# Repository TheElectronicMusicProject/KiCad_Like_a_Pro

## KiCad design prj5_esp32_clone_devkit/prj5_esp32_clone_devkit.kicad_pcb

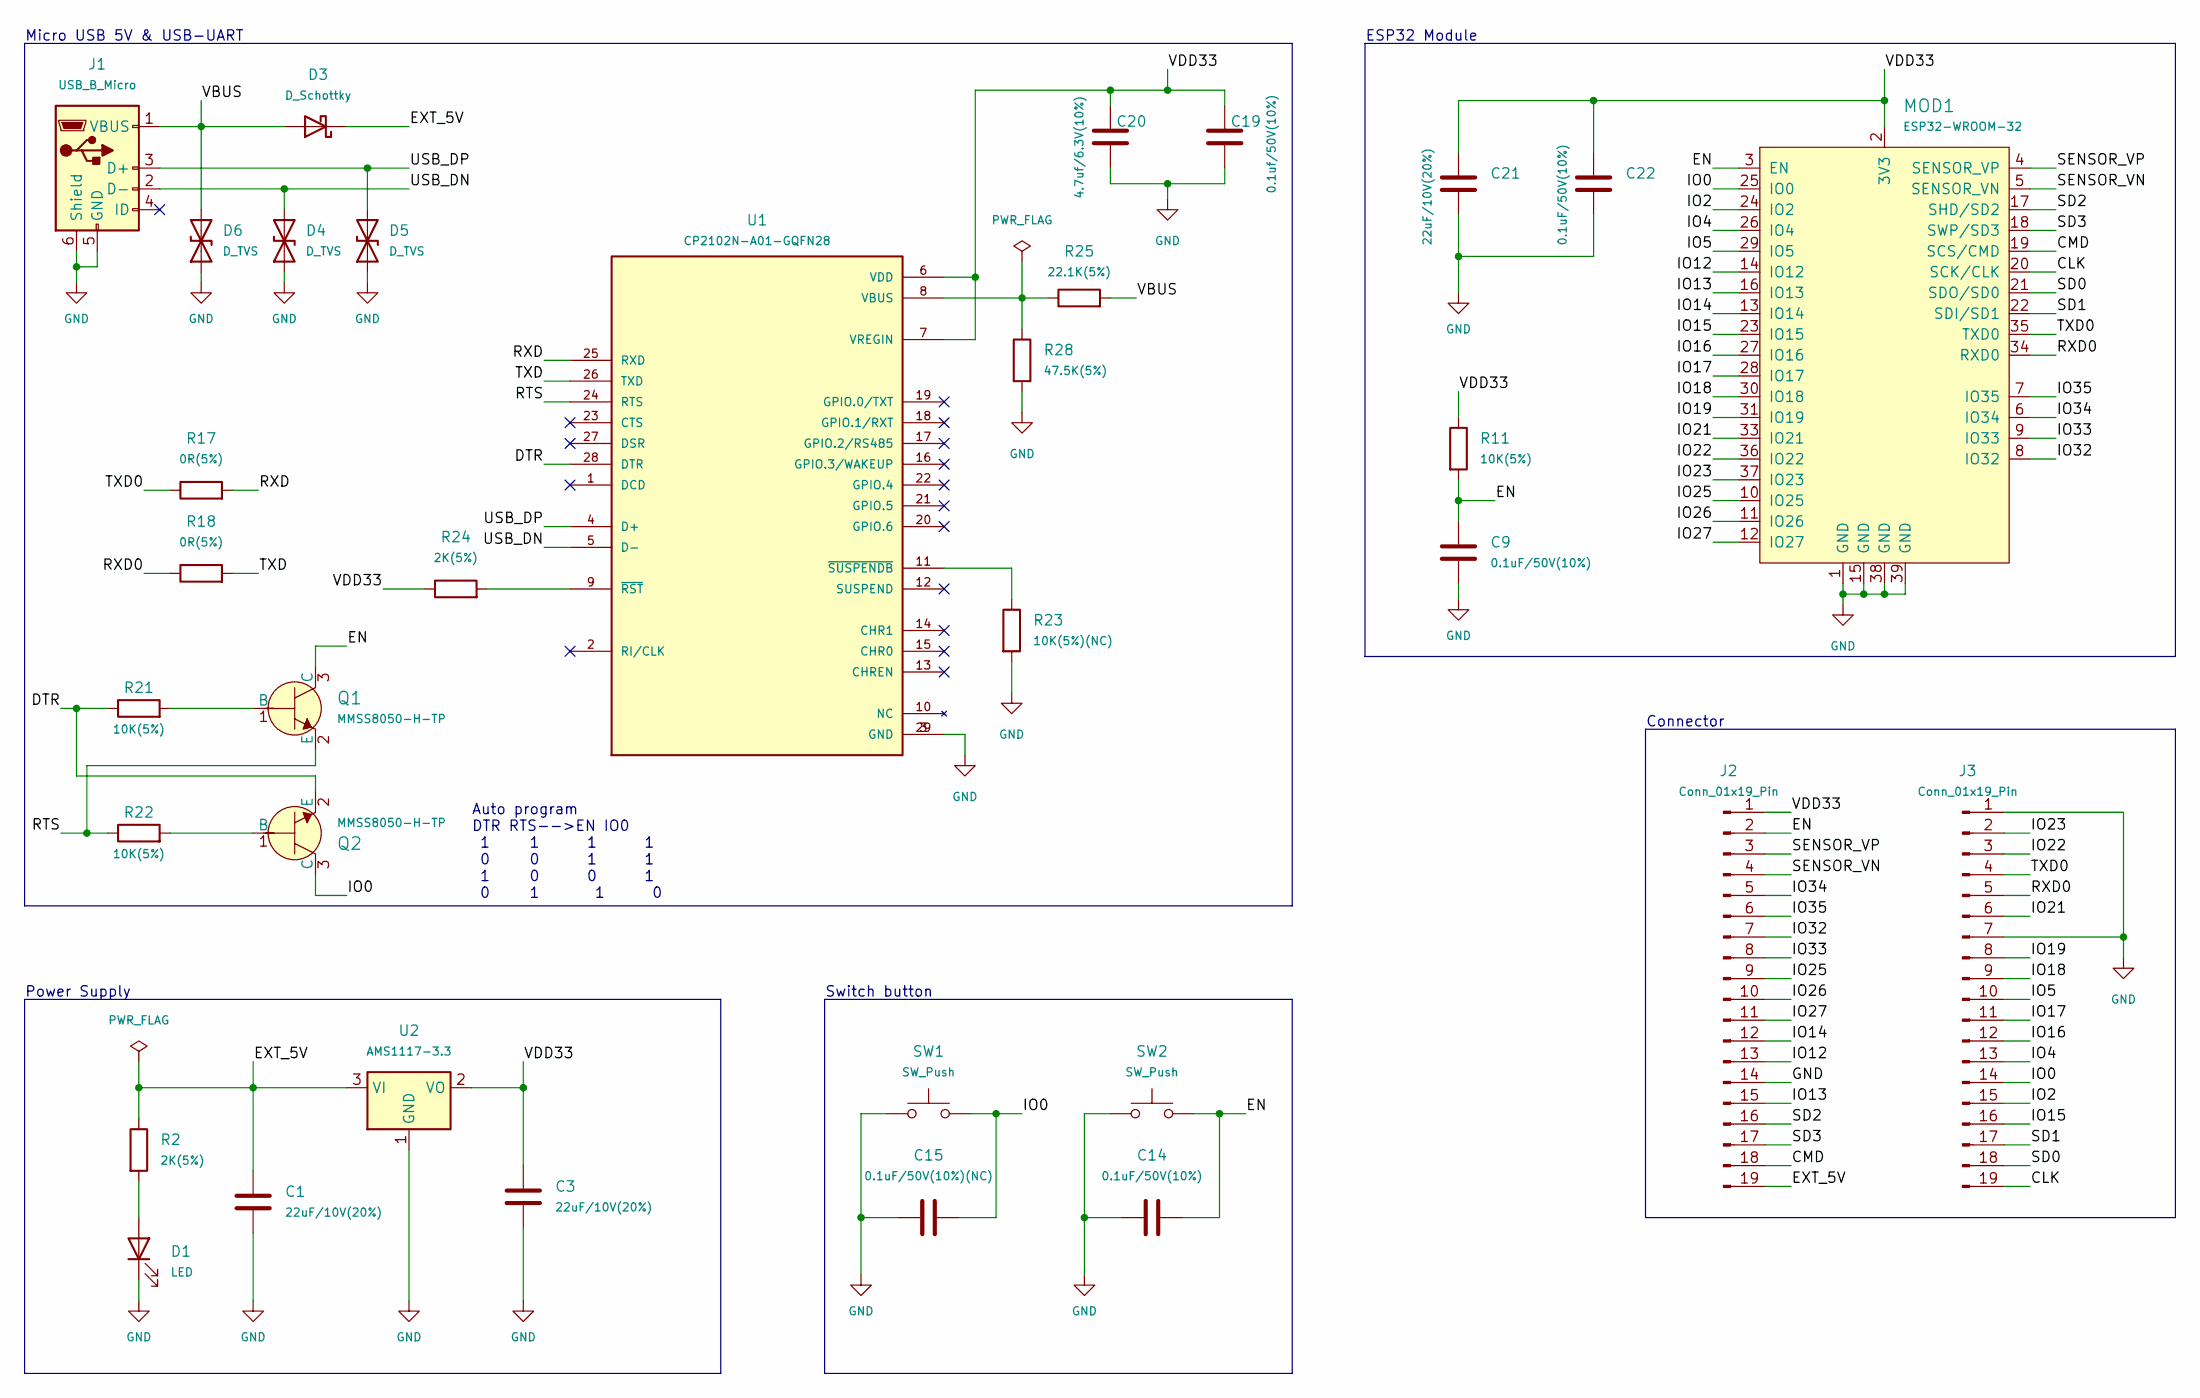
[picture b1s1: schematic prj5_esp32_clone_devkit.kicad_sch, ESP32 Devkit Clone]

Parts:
C1, C3, C21: 22uF/10V(20%); C_0603_1608Metric
C9, C14, C22: 0.1uF/50V(10%); C_0402_1005Metric
C15: 0.1uF/50V(10%)(NC); C_0402_1005Metric
C19: 0.1uf/50V(10%); C_0402_1005Metric
C20: 4.7uf/6.3V(10%); C_0402_1005Metric
D1: LED; LED_0603_1608Metric
D3: D_Schottky; D_SOD-323
D4, D5, D6: D_TVS; D_SOD-523
J1: USB_B_Micro; USB_Micro-AB_Molex_47590-0001
J2, J3: Conn_01x19_Pin; PinHeader_1x19_P2.54mm_Vertical
MOD1: ESP32-WROOM-32; ESP32-WROOM-32D; MPN ESP32-WROOM-32; Digi-Key_PN 1904-1010-1-ND
Q1, Q2: MMSS8050-H-TP; SOT-23-3; MPN MMSS8050-H-TP; Digi-Key_PN MMSS8050-H-TPMSCT-ND
R2, R24: 2K(5%); R_01005_0402Metric
R11, R21, R22: 10K(5%); R_01005_0402Metric
R17, R18: 0R(5%); R_01005_0402Metric
R23: 10K(5%)(NC); R_01005_0402Metric
R25: 22.1K(5%); R_01005_0402Metric
R28: 47.5K(5%); R_01005_0402Metric
SW1, SW2: SW_Push; SW_SPST_B3S-1000
U1: CP2102N-A01-GQFN28; TQFN-28-1EP_5x5mm_P0.5mm_EP2.7x2.7mm; PARTREV 1.0
U2: AMS1117-3.3; SOT-223-3_TabPin2

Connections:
/CLK: J3.19, MOD1.20 (SCK/CLK)
/CMD: J2.18, MOD1.19 (SCS/CMD)
/DTR: Q2.2 (E), R21.1, U1.28 (DTR)
/EN: C9.1, C14.2, J2.2, MOD1.3 (EN), Q1.3 (C), R11.2, SW2.2
/EXT_5V: C1.1, D3.1 (K), J2.19, R2.1, U2.3 (VI)
/IO0: C15.2, J3.14, MOD1.25 (IO0), Q2.3 (C), SW1.2
/IO2: J3.15, MOD1.24 (IO2)
/IO4: J3.13, MOD1.26 (IO4)
/IO5: J3.10, MOD1.29 (IO5)
/IO12: J2.13, MOD1.14 (IO12)
/IO13: J2.15, MOD1.16 (IO13)
/IO14: J2.12, MOD1.13 (IO14)
/IO15: J3.16, MOD1.23 (IO15)
/IO16: J3.12, MOD1.27 (IO16)
/IO17: J3.11, MOD1.28 (IO17)
/IO18: J3.9, MOD1.30 (IO18)
/IO19: J3.8, MOD1.31 (IO19)
/IO21: J3.6, MOD1.33 (IO21)
/IO22: J3.3, MOD1.36 (IO22)
/IO23: J3.2, MOD1.37 (IO23)
/IO25: J2.9, MOD1.10 (IO25)
/IO26: J2.10, MOD1.11 (IO26)
/IO27: J2.11, MOD1.12 (IO27)
/IO32: J2.7, MOD1.8 (IO32)
/IO33: J2.8, MOD1.9 (IO33)
/IO34: J2.5, MOD1.6 (IO34)
/IO35: J2.6, MOD1.7 (IO35)
/RTS: Q1.2 (E), R22.1, U1.24 (RTS)
/RXD: R17.2, U1.25 (RXD)
/RXD0: J3.5, MOD1.34 (RXD0), R18.1
/SD0: J3.18, MOD1.21 (SDO/SD0)
/SD1: J3.17, MOD1.22 (SDI/SD1)
/SD2: J2.16, MOD1.17 (SHD/SD2)
/SD3: J2.17, MOD1.18 (SWP/SD3)
/SENSOR_VN: J2.4, MOD1.5 (SENSOR_VN)
/SENSOR_VP: J2.3, MOD1.4 (SENSOR_VP)
/TXD: R18.2, U1.26 (TXD)
/TXD0: J3.4, MOD1.35 (TXD0), R17.1
/USB_DN: D4.2 (A2), J1.2 (D-), U1.5 (D-)
/USB_DP: D5.2 (A2), J1.3 (D+), U1.4 (D+)
/VBUS: D3.2 (A), D6.2 (A2), J1.1 (VBUS), R25.2
/VDD33: C3.1, C19.1, C20.1, C21.1, C22.1, J2.1, MOD1.2 (3V3), R11.1, R24.1, U1.6 (VDD), U1.7 (VREGIN), U2.2 (VO)
GND: C1.2, C3.2, C9.2, C14.1, C15.1, C19.2, C20.2, C21.2, C22.2, D1.1 (K), D4.1 (A1), D5.1 (A1), D6.1 (A1), J1.5 (GND), J1.6 (Shield), J2.14, J3.1, J3.7, MOD1.1 (GND), MOD1.15 (GND), MOD1.38 (GND), MOD1.39 (GND), R23.2, R28.2, SW1.1, SW2.1, U1.3 (GND), U1.29 (GND), U2.1 (GND)
unnamed: D1.2 (A), R2.2
unnamed: Q1.1 (B), R21.2
unnamed: Q2.1 (B), R22.2
unnamed: R25.1, R28.1, U1.8 (VBUS)
unnamed: R24.2, U1.9 (~RST)
unnamed: R23.1, U1.11 (~SUSPENDB)

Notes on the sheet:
Switch button
Micro USB 5V & USB-UART
Power Supply
Auto program DTR RTS-->EN IO0 1 1 1 1 0 0 1 1 1 0 0 1 0 1 1 0
Connector
ESP32 Module

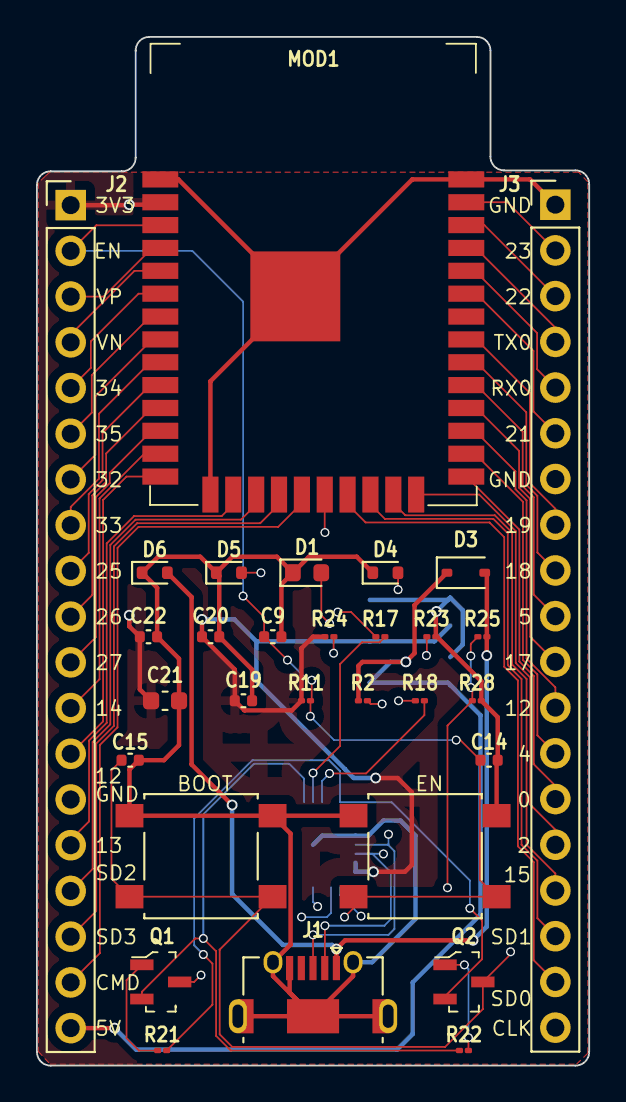
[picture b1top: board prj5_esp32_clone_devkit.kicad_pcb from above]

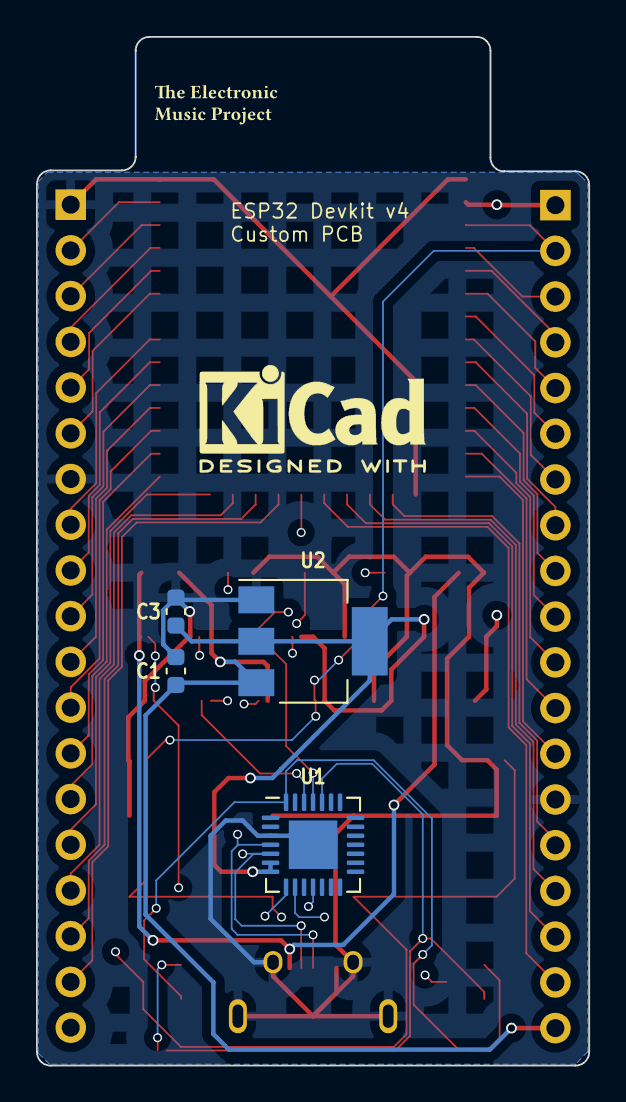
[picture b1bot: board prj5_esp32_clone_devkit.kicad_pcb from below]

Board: 4 copper layers, 30.7 x 57.2 mm, 36 parts (6 on the bottom side), 49 nets.

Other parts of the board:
G1: LOGO; The_Electronic_Music_Project_silk_logo
REF1: KiCad-Logo2_5mm_SilkScreen

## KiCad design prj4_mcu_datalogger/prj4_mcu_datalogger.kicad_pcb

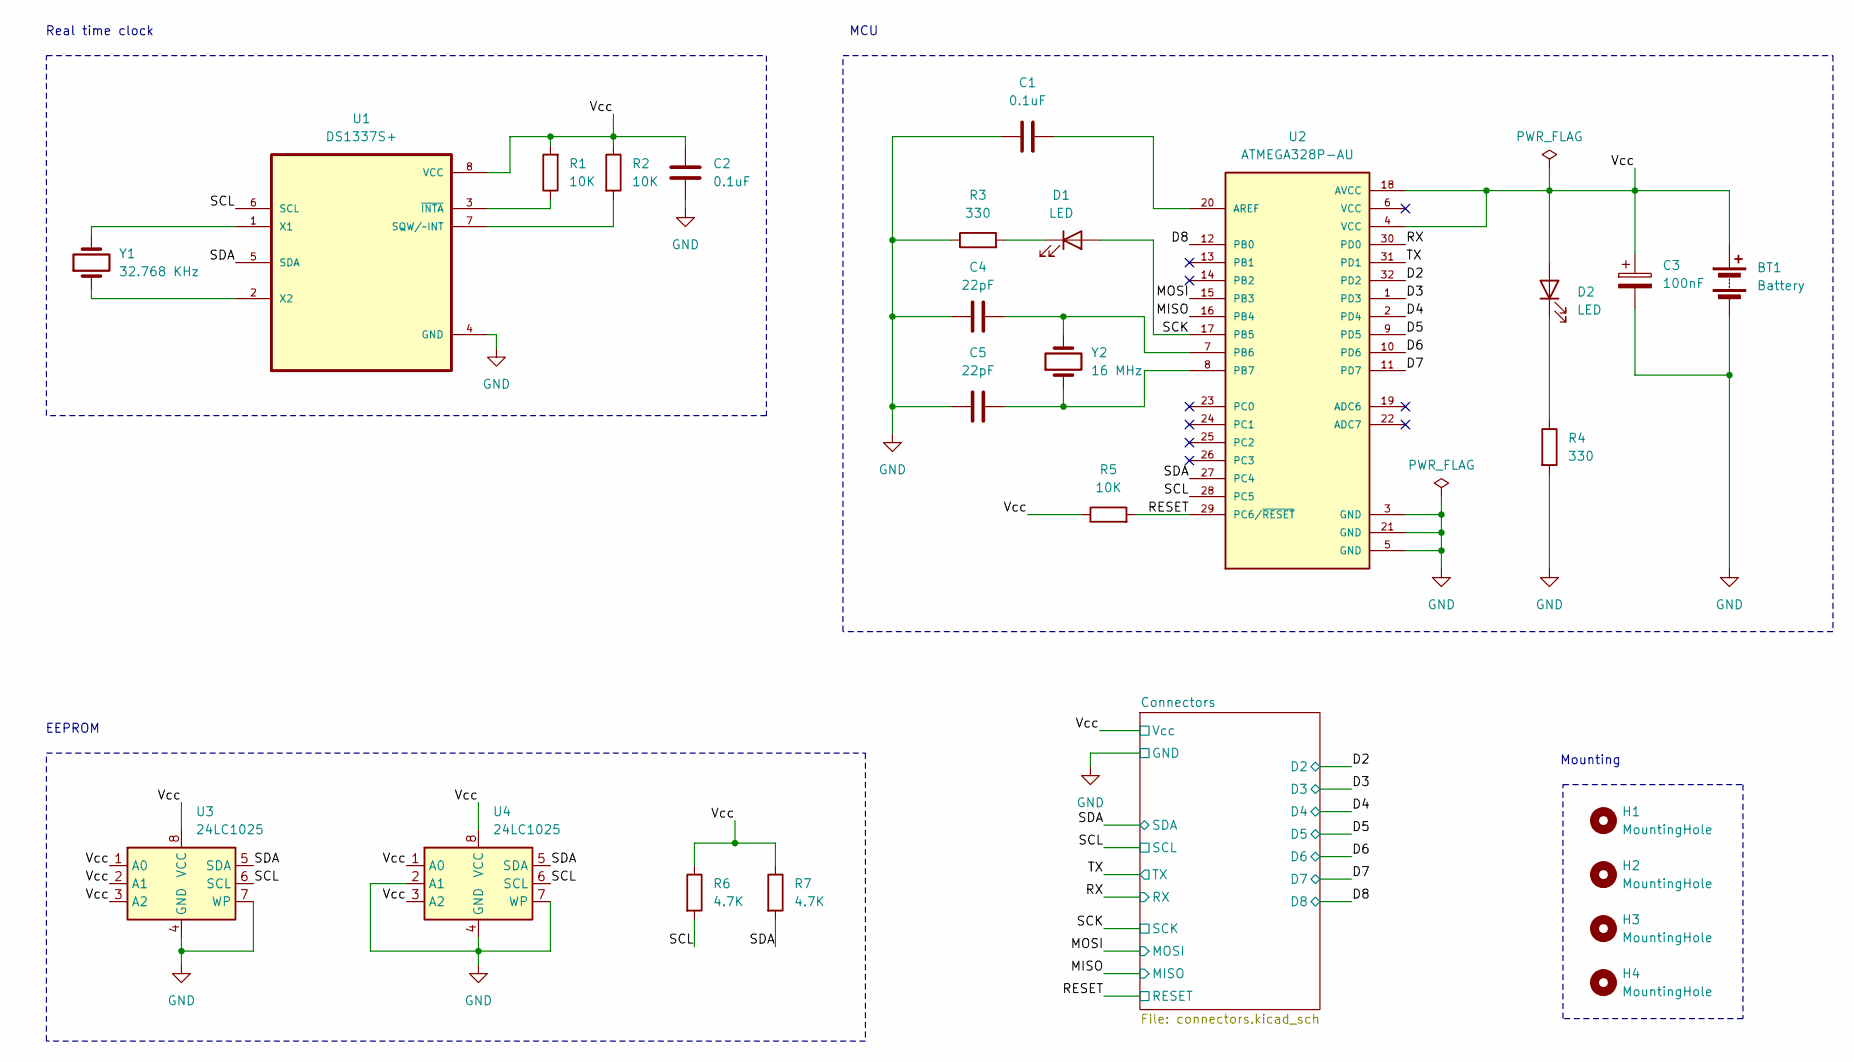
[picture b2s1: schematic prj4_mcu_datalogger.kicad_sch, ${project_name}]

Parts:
BT1: Battery; PinHeader_1x02_P2.54mm_Vertical
C1, C2: 0.1uF; C_0805_2012Metric
C3: 100nF; C_0805_2012Metric
C4, C5: 22pF; C_0805_2012Metric
D1, D2: LED; LED_0805_2012Metric
H1, H2, H3, H4: MountingHole; MountingHole_2.1mm
R1, R2, R5: 10K; R_0805_2012Metric
R3, R4: 330; R_0805_2012Metric
R6, R7: 4.7K; R_0805_2012Metric
U1: DS1337S+; SOIC127P600X175-8N
U2: ATMEGA328P-AU; QFP80P900X900X120-32N
U3, U4: 24LC1025; SOIC-8_5.23x5.23mm_P1.27mm
Y1: 32.768 KHz; Crystal_SMD_5032-2Pin_5.0x3.2mm_HandSoldering
Y2: 16 MHz; Crystal_SMD_5032-2Pin_5.0x3.2mm_HandSoldering

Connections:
/D2: U2.32 (PD2); also elsewhere on the board
/D3: U2.1 (PD3); also elsewhere on the board
/D4: U2.2 (PD4); also elsewhere on the board
/D5: U2.9 (PD5); also elsewhere on the board
/D6: U2.10 (PD6); also elsewhere on the board
/D7: U2.11 (PD7); also elsewhere on the board
/D8: U2.12 (PB0); also elsewhere on the board
/MISO: U2.16 (PB4); also elsewhere on the board
/MOSI: U2.15 (PB3); also elsewhere on the board
/RESET: R5.2, U2.29 (PC6/~RESET); also elsewhere on the board
/RX: U2.30 (PD0); also elsewhere on the board
/SCK: D1.2 (A), U2.17 (PB5); also elsewhere on the board
/SCL: R6.2, U1.6 (SCL), U2.28 (PC5), U3.6 (SCL), U4.6 (SCL); also elsewhere on the board
/SDA: R7.2, U1.5 (SDA), U2.27 (PC4), U3.5 (SDA), U4.5 (SDA); also elsewhere on the board
/TX: U2.31 (PD1); also elsewhere on the board
/Vcc: BT1.1 (+), C2.1, C3.1, D2.2 (A), R1.2, R2.1, R5.1, R6.1, R7.1, U1.8 (VCC), U2.4 (VCC), U2.18 (AVCC), U3.1 (A0), U3.2 (A1), U3.3 (A2), U3.8 (VCC), U4.1 (A0), U4.3 (A2), U4.8 (VCC); also elsewhere on the board
GND: BT1.2 (-), C1.1, C2.2, C3.2, C4.1, C5.1, R3.1, R4.2, U1.4 (GND), U2.3 (GND), U2.5 (GND), U2.21 (GND), U3.4 (GND), U3.7 (WP), U4.2 (A1), U4.4 (GND), U4.7 (WP); also elsewhere on the board
unnamed: D1.1 (K), R3.2
unnamed: D2.1 (K), R4.1
unnamed: R2.2, U1.7 (SQW/~INT)
unnamed: U1.1 (X1), Y1.2
unnamed: U1.2 (X2), Y1.1
unnamed: R1.1, U1.3 (~INTA)
unnamed: C1.2, U2.20 (AREF)
unnamed: C4.2, U2.7 (PB6), Y2.2
unnamed: C5.2, U2.8 (PB7), Y2.1

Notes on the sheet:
MCU
Mounting
Real time clock
EEPROM

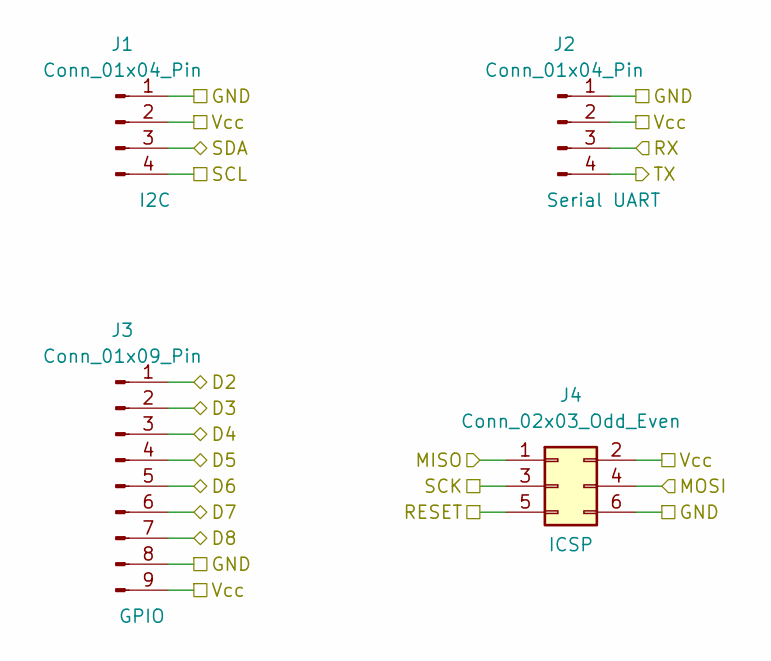
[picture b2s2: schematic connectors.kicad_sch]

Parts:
J1, J2: Conn_01x04_Pin; PinHeader_1x04_P2.54mm_Vertical
J3: Conn_01x09_Pin; PinHeader_1x09_P2.54mm_Vertical
J4: Conn_02x03_Odd_Even; PinHeader_2x03_P2.54mm_Vertical

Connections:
/D2: J3.1; also elsewhere on the board
/D3: J3.2; also elsewhere on the board
/D4: J3.3; also elsewhere on the board
/D5: J3.4; also elsewhere on the board
/D6: J3.5; also elsewhere on the board
/D7: J3.6; also elsewhere on the board
/D8: J3.7; also elsewhere on the board
/MISO: J4.1; also elsewhere on the board
/MOSI: J4.4; also elsewhere on the board
/RESET: J4.5; also elsewhere on the board
/RX: J2.3; also elsewhere on the board
/SCK: J4.3; also elsewhere on the board
/SCL: J1.4; also elsewhere on the board
/SDA: J1.3; also elsewhere on the board
/TX: J2.4; also elsewhere on the board
/Vcc: J1.2, J2.2, J3.9, J4.2; also elsewhere on the board
GND: J1.1, J2.1, J3.8, J4.6; also elsewhere on the board

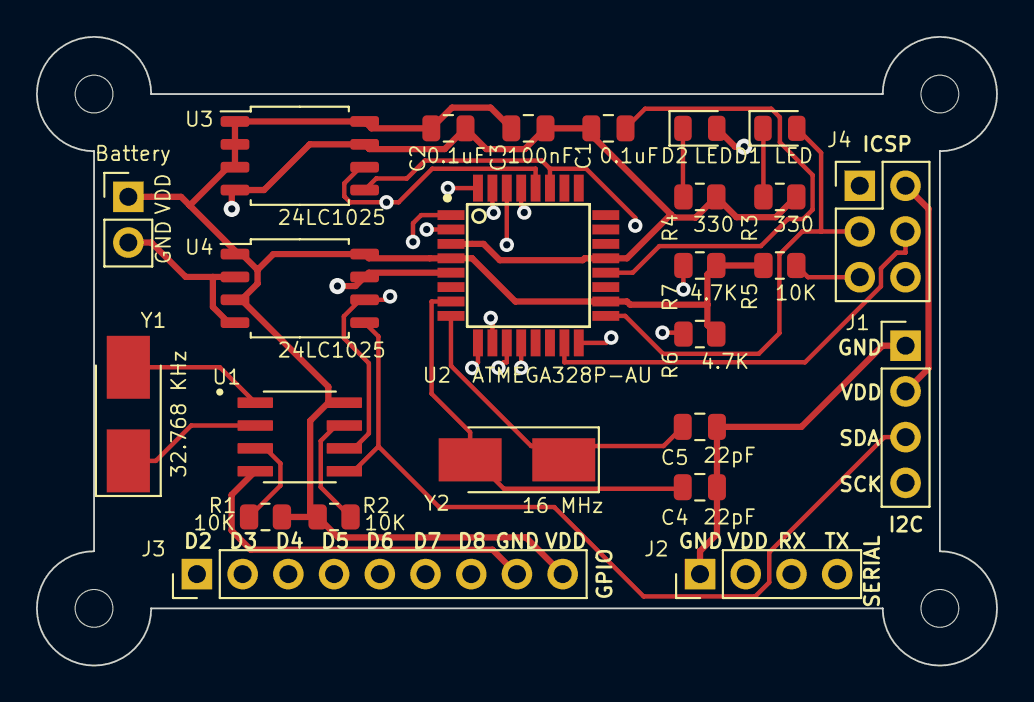
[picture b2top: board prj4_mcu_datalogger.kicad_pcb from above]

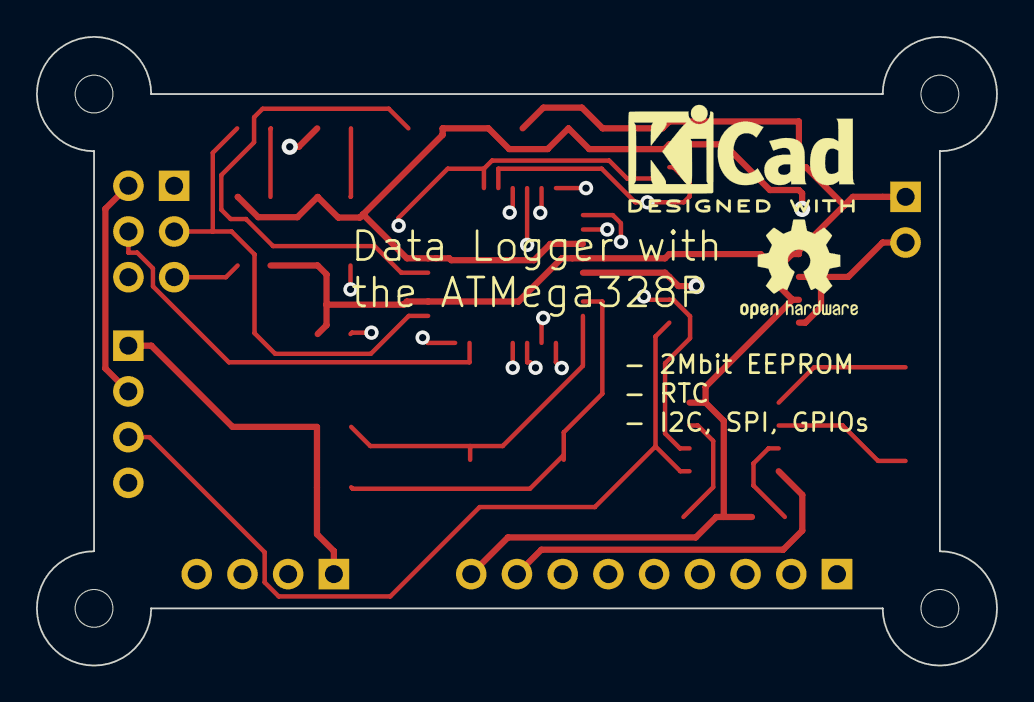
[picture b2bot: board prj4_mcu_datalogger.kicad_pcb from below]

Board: 4 copper layers, 53.3 x 34.9 mm, 31 parts (2 on the bottom side), 26 nets.

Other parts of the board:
REF1: KiCad-Logo2_5mm_SilkScreen
REF2: OSHW-Logo2_7.3x6mm_SilkScreen

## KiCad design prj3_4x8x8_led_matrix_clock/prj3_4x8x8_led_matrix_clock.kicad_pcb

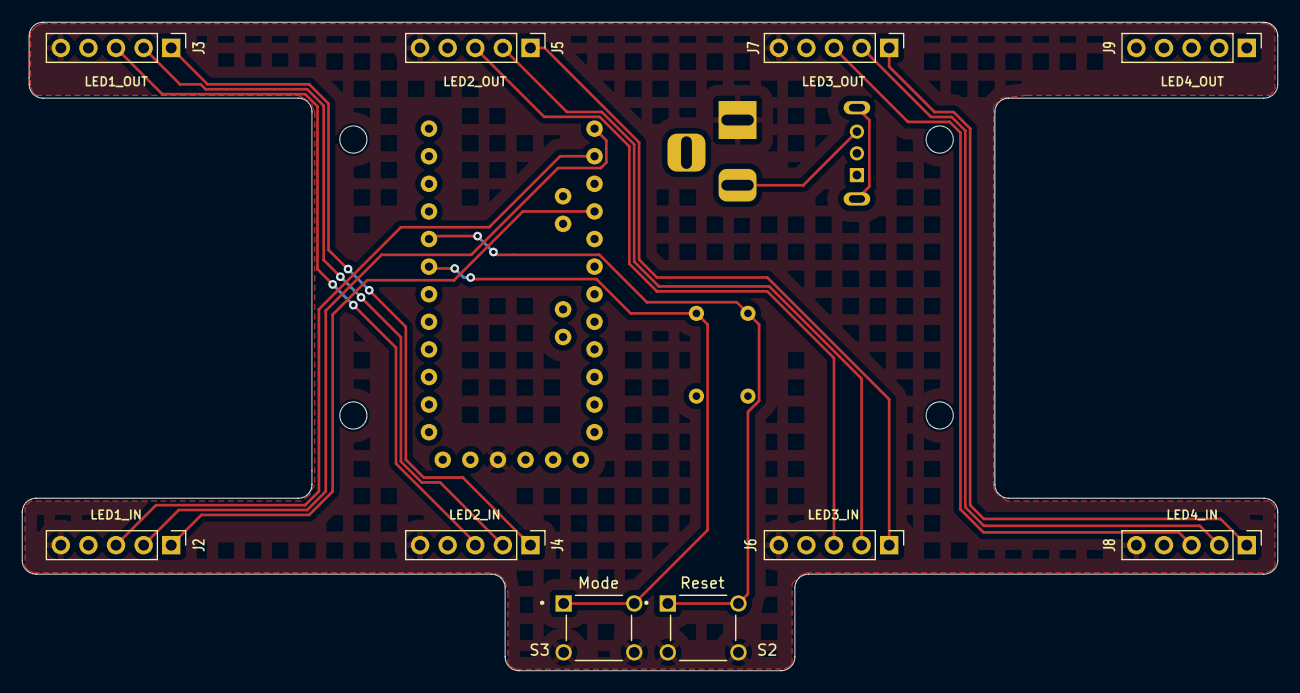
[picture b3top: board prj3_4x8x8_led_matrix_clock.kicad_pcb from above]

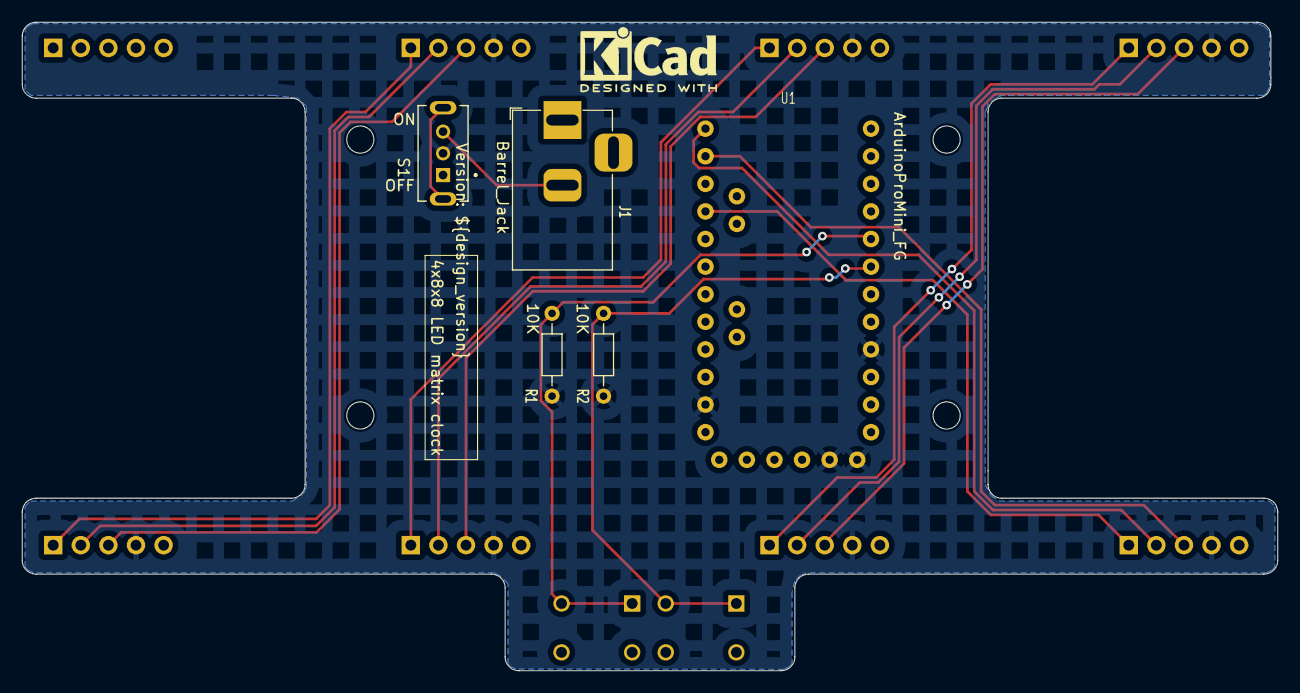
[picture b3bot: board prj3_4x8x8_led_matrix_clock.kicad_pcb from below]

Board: 2 copper layers, 115.6 x 59.7 mm, 19 parts (5 on the bottom side), 17 nets.

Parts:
H1, H2, H3, H4: MountingHole; MountingHole_2.5mm
J1: Barrel_Jack; BarrelJack_Horizontal
J2: LED1_IN; PinHeader_1x05_P2.54mm_Vertical
J3: LED1_OUT; PinHeader_1x05_P2.54mm_Vertical
J4: LED2_IN; PinHeader_1x05_P2.54mm_Vertical
J5: LED2_OUT; PinHeader_1x05_P2.54mm_Vertical
J6: LED3_IN; PinHeader_1x05_P2.54mm_Vertical
J7: LED3_OUT; PinHeader_1x05_P2.54mm_Vertical
J8: LED4_IN; PinHeader_1x05_P2.54mm_Vertical
J9: LED4_OUT; PinHeader_1x05_P2.54mm_Vertical
R1, R2: 10K; R_Axial_DIN0204_L3.6mm_D1.6mm_P7.62mm_Horizontal
S1: SS12D07VG4; SW_SS12D07VG4
S2, S3: 1825967-1; SW_1825967-1
U1: ArduinoProMini_FG

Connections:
/CLK0: J2.1, U1.6 (SCK)
/CLK1: J3.1, J4.1
/CLK2: J5.1, J6.1
/CLK3: J7.1, J8.1
/CS0: J2.2, U1.17 (D10)
/CS1: J3.2, J4.2
/CS2: J5.2, J6.2
/CS3: J7.2, J8.2
/DIN0: J2.3, U1.8 (MOSI)
/DIN1: J3.3, J4.3
/DIN2: J5.3, J6.3
/DIN3: J7.3, J8.3
/MODE_SELECT: R2.2, S3.1, S3.2, U1.11 (D4)
/TIMER_RESET: R1.2, S2.1, S2.2, U1.12 (D5)
/Vcc: J1.1, J2.5, J3.5, J4.5, J5.5, J6.5, J7.5, J8.5, S2.3, S2.4, S3.3, S3.4, U1.1 (Vcc)
GND: J2.4, J3.4, J4.4, J5.4, J6.4, J7.4, J8.4, R1.1, R2.1, S1.2, U1.18 (GND_2), U1.19 (GND_1), U1.20 (GND), U1.21 (GND)
unnamed: J1.2, S1.3

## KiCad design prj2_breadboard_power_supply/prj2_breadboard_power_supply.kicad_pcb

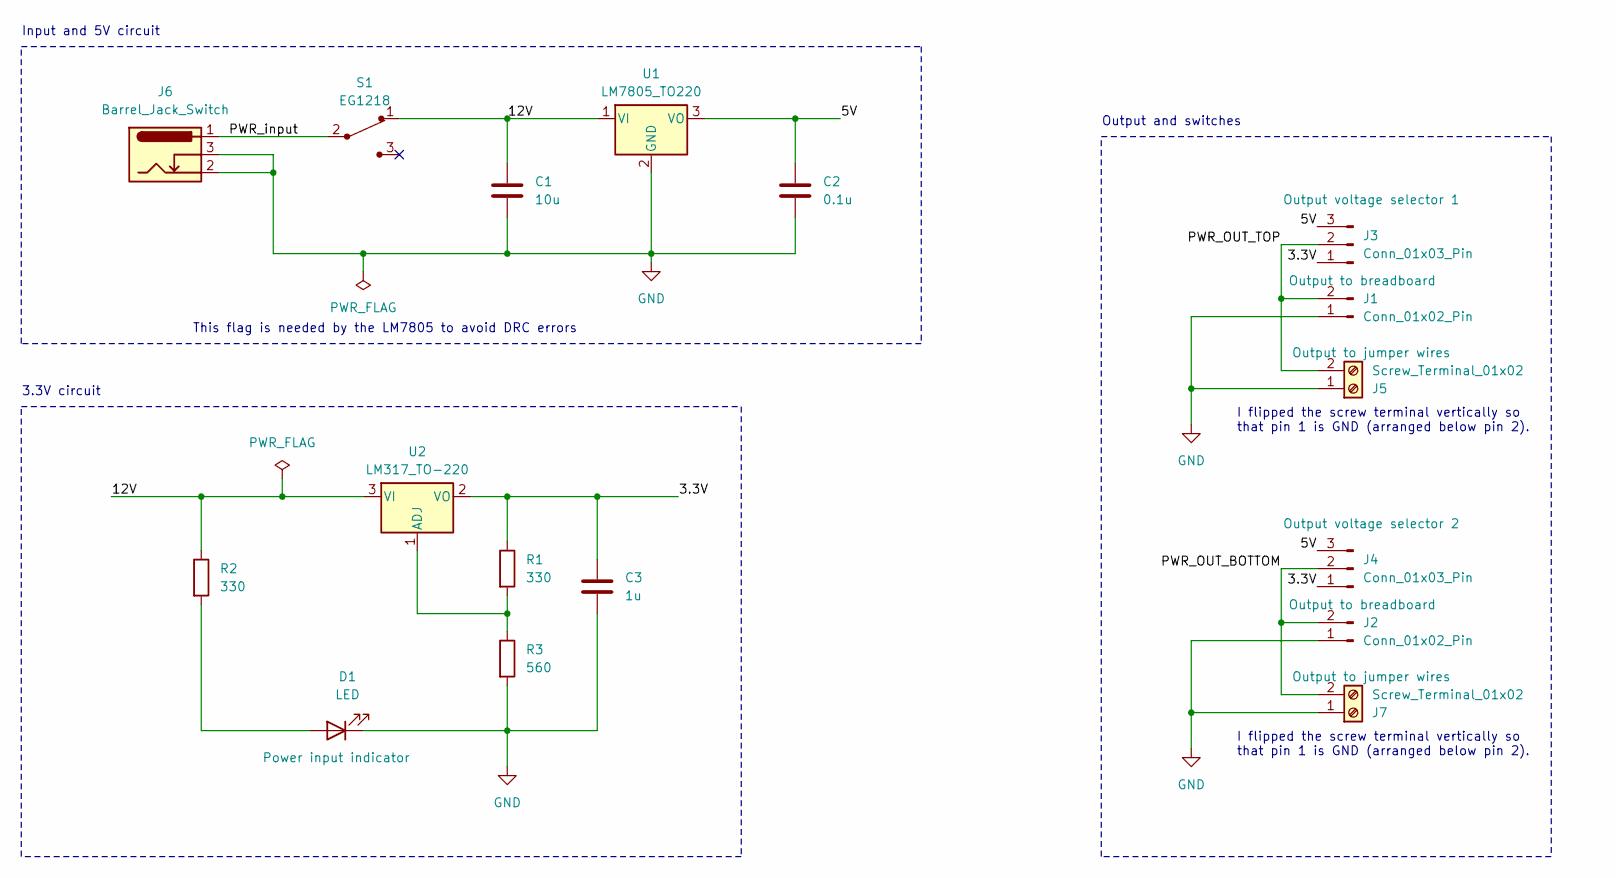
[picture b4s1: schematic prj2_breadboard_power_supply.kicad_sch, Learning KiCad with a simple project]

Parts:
C1: 10u; C_Disc_D3.0mm_W1.6mm_P2.50mm
C2: 0.1u; C_Disc_D3.0mm_W1.6mm_P2.50mm
C3: 1u; C_Disc_D3.0mm_W1.6mm_P2.50mm
D1: LED; LED_D5.0mm
J1, J2: Conn_01x02_Pin; PinHeader_1x02_P2.54mm_Vertical
J3, J4: Conn_01x03_Pin; PinHeader_1x03_P2.54mm_Vertical
J5, J7: Screw_Terminal_01x02; TerminalBlock_bornier-2_P5.08mm
J6: Barrel_Jack_Switch; BarrelJack_Horizontal
R1, R2: 330; R_Axial_DIN0204_L3.6mm_D1.6mm_P7.62mm_Horizontal
R3: 560; R_Axial_DIN0204_L3.6mm_D1.6mm_P7.62mm_Horizontal
S1: EG1218; Switch_Slide_11.6x4mm_EG1218; MPN EG1218; Digi-Key_PN EG1903-ND
U1: LM7805_TO220; TO-220-3_Vertical
U2: LM317_TO-220; TO-220-3_Vertical

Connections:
/3.3V: C3.1, J3.1, J4.1, R1.1, U2.2 (VO)
/5V: C2.1, J3.3, J4.3, U1.3 (VO)
/12V: C1.1, R2.1, S1.1, U1.1 (VI), U2.3 (VI)
/PWR_OUT_BOTTOM: J2.2, J4.2, J7.2
/PWR_OUT_TOP: J1.2, J3.2, J5.2
/PWR_input: J6.1, S1.2
GND: C1.2, C2.2, C3.2, D1.1 (K), J1.1, J2.1, J5.1, J6.2, J6.3, J7.1, R3.2, U1.2 (GND)
unnamed: D1.2 (A), R2.2
unnamed: R1.2, R3.1, U2.1 (ADJ)

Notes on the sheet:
Output and switches
I flipped the screw terminal vertically so that pin 1 is GND (arranged below pin 2).
Input and 5V circuit
3.3V circuit
This flag is needed by the LM7805 to avoid DRC errors

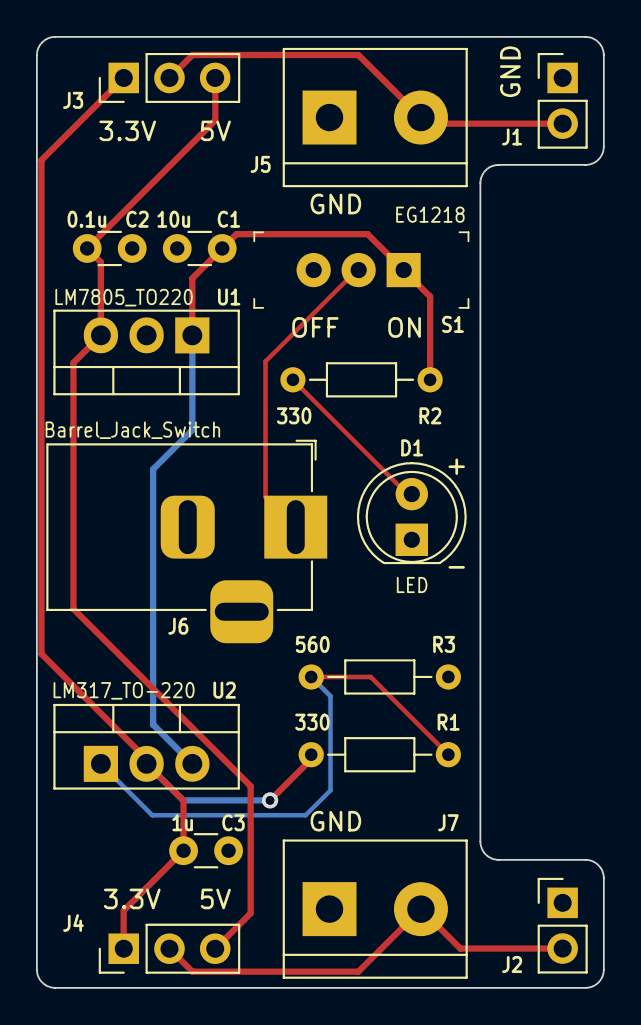
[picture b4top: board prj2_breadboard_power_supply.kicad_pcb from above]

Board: 2 copper layers, 31.5 x 52.8 mm, 17 parts (0 on the bottom side), 9 nets.

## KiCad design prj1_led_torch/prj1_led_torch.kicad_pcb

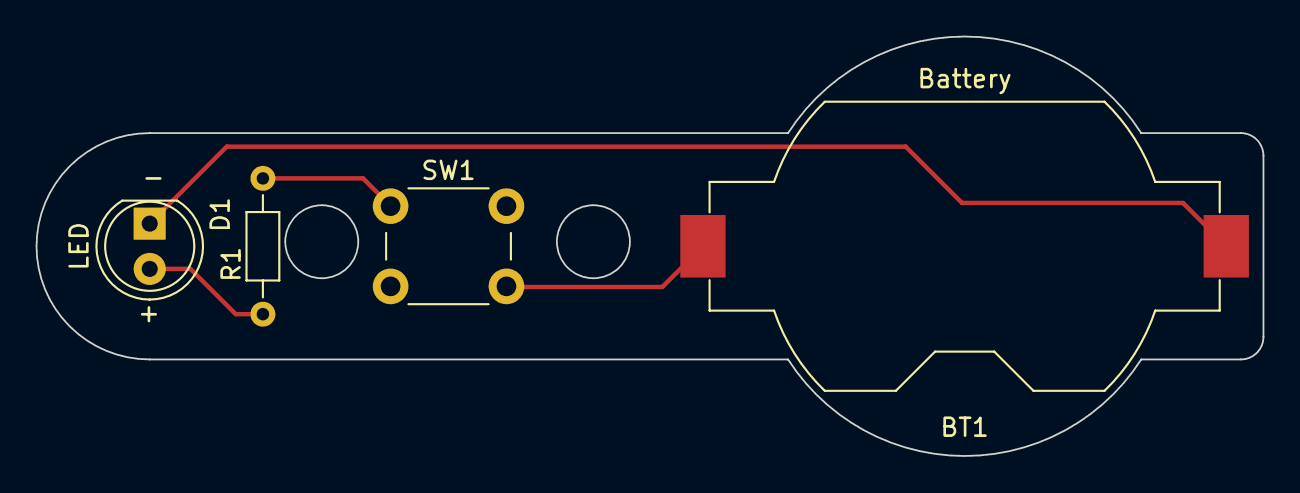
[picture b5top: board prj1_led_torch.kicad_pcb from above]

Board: 2 copper layers, 68.8 x 23.5 mm, 4 parts (0 on the bottom side), 4 nets.

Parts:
BT1: Battery; BatteryHolder_Keystone_1058_1x2032
D1: LED; LED_D5.0mm
R1: R; R_Axial_DIN0204_L3.6mm_D1.6mm_P7.62mm_Horizontal
SW1: SW_SPST; SW_PUSH_6mm_H5mm

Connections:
/LED_anode: D1.2 (A), R1.1
/LED_cathode: BT1.2 (-), D1.1 (K)
/bat_pos: BT1.1 (+), SW1.2 (B)
unnamed: R1.2, SW1.1 (A)
